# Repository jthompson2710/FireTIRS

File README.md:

# FireTIRS

This respository contains the hardware and software produced during the development of the Fire Thermal InfraRed Spectrometer (FireTIRS) imaging instrument as part of a NASA ESTO FireTech project (grant: 80NSSC23K1544)

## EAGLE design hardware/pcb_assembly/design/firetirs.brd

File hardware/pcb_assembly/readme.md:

## FireTIRS PCB Assembly
This directory contains the design files and documentation necessary to build the FireTIRS PCB Assembly.

* ```design``` : Contains the Eagle version 7.7 CAD source design files (schematic and layout).
* ```documentation``` : Contains supporting documentation files including Bill-of-Material (BOM), component load list, component centroid file, stack-up information and PDF versions of the schematic and layout.
* ```gerbers``` : Contain the PCB gerber files.
* ```stencils``` : Contain the stencil gerber files.

### Printed Circuit Board

* Layer Count: 4
* Material: FR4
* Dimensions: 6.5" x 5.5" (165.1mm x  139.7mm)
* Thickness: 0.062" (1.6mm) thickness

#### Gerber files

| File Suffix | Description |
| --- | --- |
| GBL | Bottom Copper (Layer 4) |
| GBO | Bottom Silkscreen |
| GBS | Bottom Soldermask |
| GL2 | Inner Layer 2 Copper |
| GL3 | Inner Layer 3 Copper |
| GML | Mill layer (dimensional) |
| GTL | Top Copper (Layer 1) |
| GTS | Top Soldermask |
| GTO | Top Silkscreen |
| TXT | Drill file |

### Assembly
The PCB Assembly has surface-mount parts on top and bottom and through-hole parts on top.

(note: Raspberry Pi 4 Compute Module spacers shown are not part of the assembly at this stage)

#### Stencil files
 
| File Suffix | Description |
| --- | --- |
| GBP | Bottom Paste |
| GTP | Top Paste |

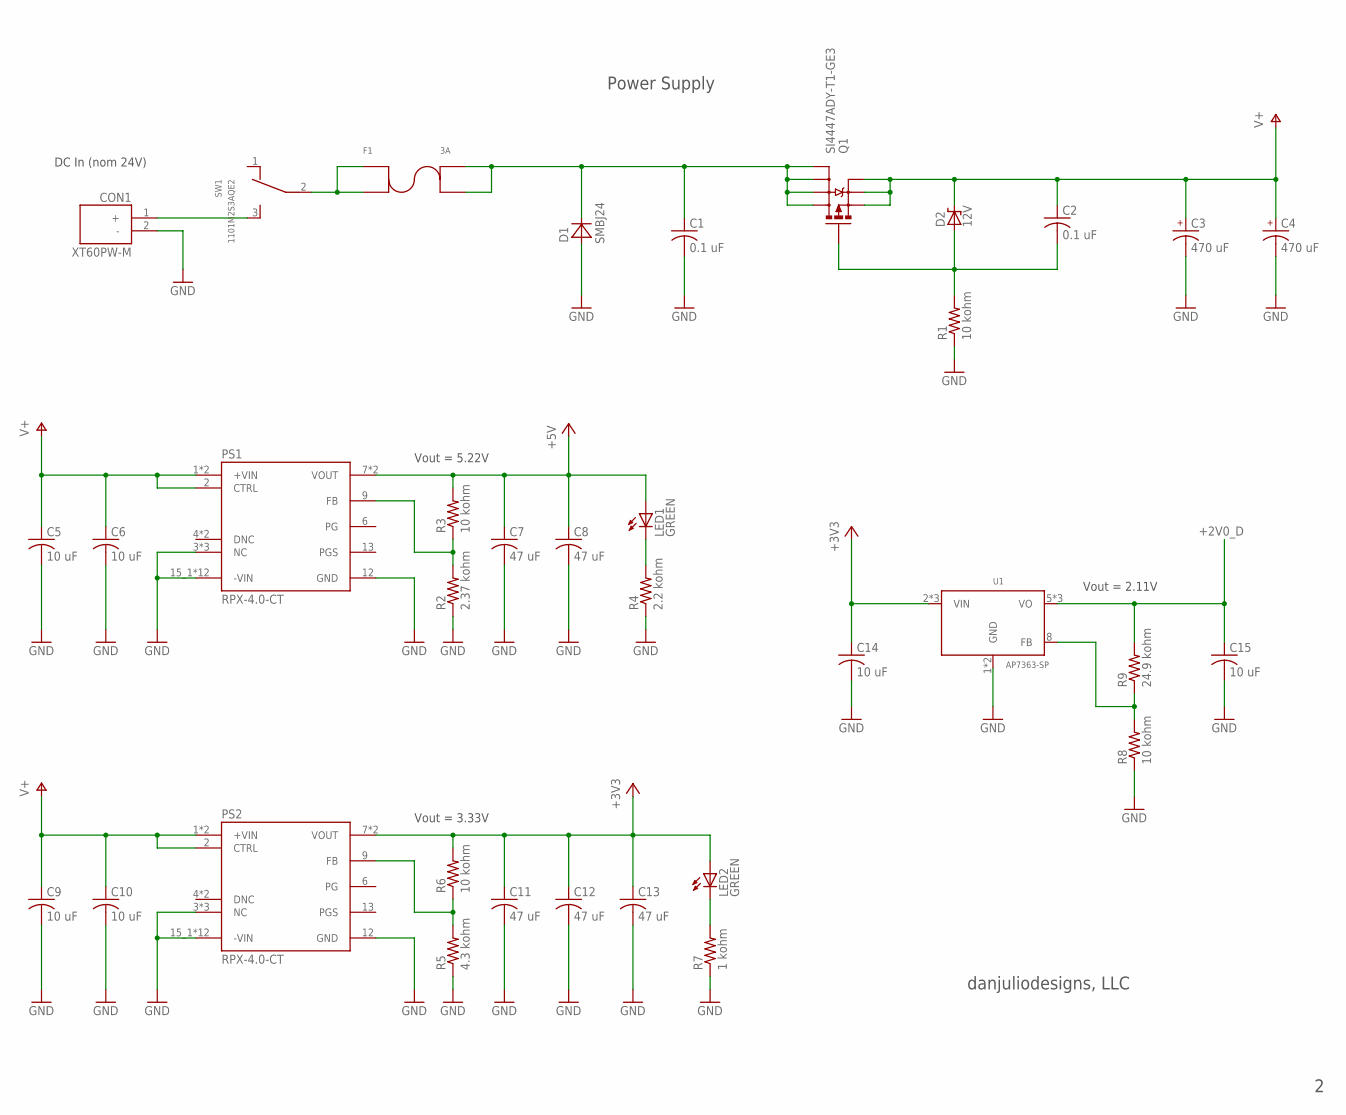
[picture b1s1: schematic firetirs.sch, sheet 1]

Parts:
C1, C2: 0.1 uF; C0805
C3, C4: 470 uF; ECAP-0810
C5, C6, C9, C10: 10 uF; C0805
C7, C8, C11, C12, C13: 47 uF; C0805
C14, C15: 10 uF; C0603
CON1: XT60PW-M; AMASS_XT60PW-M
D1: SMBJ24; DO214AA
D2: 12V; SOD123
F1: 3A; FUSE_5_20_MM_SIDE
LED1, LED2: GREEN; CHIPLED_0603
PS1, PS2: RPX-4.0-CT; CONV_RPX-4.0-CT
Q1: SI4447ADY-T1-GE3; SO8
R1, R3, R6, R8: 10 kohm; R0603
R2: 2.37 kohm; R0603
R4: 2.2 kohm; R0603
R5: 4.3 kohm; R0603
R7: 1 kohm; R0603
R9: 24.9 kohm; R0603
SW1: 1101M2S3AQE2; SIDE_PWR_SPDT
U1: AP7363-SP; SO8_PAD

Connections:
+2V0_D: C15.1, R9.2, U1.5 (VO), U1.6 (VO), U1.7 (VO); also elsewhere on the board
+3V3: C11.1, C12.1, C13.1, C14.1, LED2.A, PS2.7 (VOUT), PS2.8 (VOUT), R6.2, U1.2 (VIN), U1.3 (VIN), U1.4 (VIN); also elsewhere on the board
+5V: C7.1, C8.1, LED1.A, PS1.7 (VOUT), PS1.8 (VOUT), R3.2; also elsewhere on the board
GND: C1.2, C3.- (2), C4.- (2), C5.2, C6.2, C7.2, C8.2, C9.2, C10.2, C11.2, C12.2, C13.2, C14.2, C15.2, CON1.2 (-), D1.A, PS1.3 (NC), PS1.10 (NC), PS1.11 (NC), PS1.12 (GND), PS1.15_1 (-VIN), PS1.15_2 (-VIN), PS1.15_3 (-VIN), PS1.15_4 (-VIN), PS1.15_5 (-VIN), PS1.15_6 (-VIN), PS1.15_7 (-VIN), PS1.15_8 (-VIN), PS1.15_9 (-VIN), PS1.15_10 (-VIN), PS1.15_11 (-VIN), PS1.15_12 (-VIN), PS2.3 (NC), PS2.10 (NC), PS2.11 (NC), PS2.12 (GND), PS2.15_1 (-VIN), PS2.15_2 (-VIN), PS2.15_3 (-VIN), PS2.15_4 (-VIN), PS2.15_5 (-VIN), PS2.15_6 (-VIN), PS2.15_7 (-VIN), PS2.15_8 (-VIN), PS2.15_9 (-VIN), PS2.15_10 (-VIN), PS2.15_11 (-VIN), PS2.15_12 (-VIN), R1.1, R2.1, R4.1, R5.1, R7.1, R8.1, U1.1 (GND), U1.PAD (GND); also elsewhere on the board
unnamed: CON1.1 (+), SW1.3
unnamed: F1.1A (1), F1.1B (2), SW1.2
unnamed: C1.1, D1.C, F1.2A (3), F1.2B (4), Q1.5 (D1), Q1.6 (D2), Q1.7 (D3), Q1.8 (D4)
unnamed: C2.2, D2.A, Q1.4 (G), R1.2
unnamed: LED1.C, R4.2
unnamed: LED2.C, R7.2
unnamed: PS1.9 (FB), R2.2, R3.1
unnamed: R8.2, R9.1, U1.8 (FB)
unnamed: PS2.9 (FB), R5.2, R6.1
V+: C2.1, C3.+ (1), C4.+ (1), C5.1, C6.1, C9.1, C10.1, D2.C, PS1.1 (+VIN), PS1.2 (CTRL), PS1.14 (+VIN), PS2.1 (+VIN), PS2.2 (CTRL), PS2.14 (+VIN), Q1.1 (S1), Q1.2 (S2), Q1.3 (S3)

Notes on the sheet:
Vout = 5.22V
Vout = 3.33V
Power Supply
Vout = 2.11V
DC In (nom 24V)
danjuliodesigns, LLC

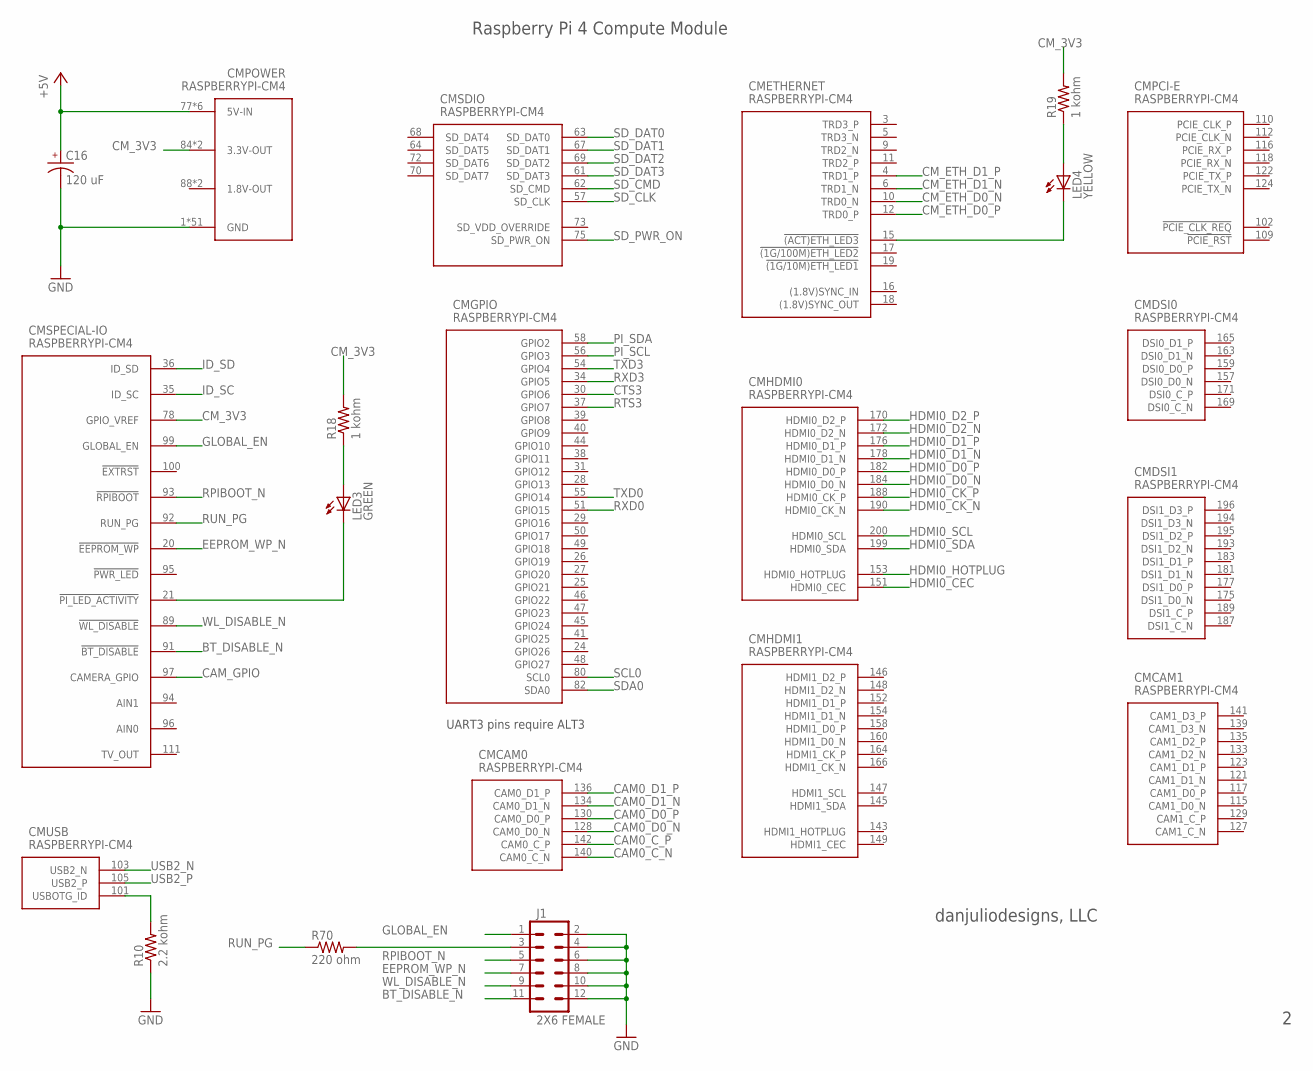
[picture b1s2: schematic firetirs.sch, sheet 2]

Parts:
C16: 120 uF; ECAP-0606
CM: RASPBERRYPI-CM4
J1: 2X6 FEMALE; 2X6
LED3: GREEN; CHIPLED_0603
LED4: YELLOW; CHIPLED_0603
R10: 2.2 kohm; R0603
R18, R19: 1 kohm; R0603
R70: 220 ohm; R0603

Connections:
1.8V-OUT: CM.88 (1.8V-OUT), CM.90 (1.8V-OUT)
+5V: C16.+ (1), CM.77 (5V-IN), CM.79 (5V-IN), CM.81 (5V-IN), CM.83 (5V-IN), CM.85 (5V-IN), CM.87 (5V-IN); also elsewhere on the board
BT_DISABLE_N: CM.91 (!BT_DISABLE), J1.11
CAM0_C_N: CM.140 (CAM0_C_N); also elsewhere on the board
CAM0_C_P: CM.142 (CAM0_C_P); also elsewhere on the board
CAM0_D0_N: CM.128 (CAM0_D0_N); also elsewhere on the board
CAM0_D0_P: CM.130 (CAM0_D0_P); also elsewhere on the board
CAM0_D1_N: CM.134 (CAM0_D1_N); also elsewhere on the board
CAM0_D1_P: CM.136 (CAM0_D1_P); also elsewhere on the board
CAM_GPIO: CM.97 (CAMERA_GPIO); also elsewhere on the board
CM_3V3: CM.78 (GPIO_VREF), CM.84 (3.3V-OUT), CM.86 (3.3V-OUT), R18.2, R19.2; also elsewhere on the board
CM_ETH_D0_N: CM.10 (TRD0_N); also elsewhere on the board
CM_ETH_D0_P: CM.12 (TRD0_P); also elsewhere on the board
CM_ETH_D1_N: CM.6 (TRD1_N); also elsewhere on the board
CM_ETH_D1_P: CM.4 (TRD1_P); also elsewhere on the board
CTS3: CM.30 (GPIO6); also elsewhere on the board
EEPROM_WP_N: CM.20 (!EEPROM_WP), J1.7
GLOBAL_EN: CM.99 (GLOBAL_EN), J1.1
GND: C16.- (2), CM.1 (GND), CM.2 (GND), CM.7 (GND), CM.8 (GND), CM.13 (GND), CM.14 (GND), CM.22 (GND), CM.23 (GND), CM.32 (GND), CM.33 (GND), CM.42 (GND), CM.43 (GND), CM.52 (GND), CM.53 (GND), CM.59 (GND), CM.60 (GND), CM.65 (GND), CM.66 (GND), CM.71 (GND), CM.74 (GND), CM.98 (GND), CM.107 (GND), CM.108 (GND), CM.113 (GND), CM.114 (GND), CM.119 (GND), CM.120 (GND), CM.125 (GND), CM.126 (GND), CM.131 (GND), CM.132 (GND), CM.137 (GND), CM.138 (GND), CM.144 (GND), CM.150 (GND), CM.155 (GND), CM.156 (GND), CM.161 (GND), CM.162 (GND), CM.167 (GND), CM.168 (GND), CM.173 (GND), CM.174 (GND), CM.179 (GND), CM.180 (GND), CM.185 (GND), CM.186 (GND), CM.191 (GND), CM.192 (GND), CM.197 (GND), CM.198 (GND), J1.2, J1.4, J1.6, J1.8, J1.10, J1.12, R10.1; also elsewhere on the board
HDMI0_CEC: CM.151 (HDMI0_CEC); also elsewhere on the board
HDMI0_CK_N: CM.190 (HDMI0_CK_N); also elsewhere on the board
HDMI0_CK_P: CM.188 (HDMI0_CK_P); also elsewhere on the board
HDMI0_D0_N: CM.184 (HDMI0_D0_N); also elsewhere on the board
HDMI0_D0_P: CM.182 (HDMI0_D0_P); also elsewhere on the board
HDMI0_D1_N: CM.178 (HDMI0_D1_N); also elsewhere on the board
HDMI0_D1_P: CM.176 (HDMI0_D1_P); also elsewhere on the board
HDMI0_D2_N: CM.172 (HDMI0_D2_N); also elsewhere on the board
HDMI0_D2_P: CM.170 (HDMI0_D2_P); also elsewhere on the board
HDMI0_HOTPLUG: CM.153 (HDMI0_HOTPLUG); also elsewhere on the board
HDMI0_SCL: CM.200 (HDMI0_SCL); also elsewhere on the board
HDMI0_SDA: CM.199 (HDMI0_SDA); also elsewhere on the board
ID_SC: CM.35 (ID_SC); also elsewhere on the board
ID_SD: CM.36 (ID_SD); also elsewhere on the board
unnamed: CM.101 (USBOTG_ID), R10.2
unnamed: CM.21 (!PI_LED_ACTIVITY), LED3.C
unnamed: LED3.A, R18.1
unnamed: CM.15 (!(ACT)ETH_LED3), LED4.C
unnamed: LED4.A, R19.1
unnamed: J1.3, R70.2
PI_SCL: CM.56 (GPIO3); also elsewhere on the board
PI_SDA: CM.58 (GPIO2); also elsewhere on the board
RPIBOOT_N: CM.93 (!RPIBOOT), J1.5
RTS3: CM.37 (GPIO7); also elsewhere on the board
RUN_PG: CM.92 (RUN_PG), R70.1
RXD0: CM.51 (GPIO15); also elsewhere on the board
RXD3: CM.34 (GPIO5); also elsewhere on the board
SCL0: CM.80 (SCL0); also elsewhere on the board
SDA0: CM.82 (SDA0); also elsewhere on the board
SD_CLK: CM.57 (SD_CLK); also elsewhere on the board
SD_CMD: CM.62 (SD_CMD); also elsewhere on the board
SD_DAT0: CM.63 (SD_DAT0); also elsewhere on the board
SD_DAT1: CM.67 (SD_DAT1); also elsewhere on the board
SD_DAT2: CM.69 (SD_DAT2); also elsewhere on the board
SD_DAT3: CM.61 (SD_DAT3); also elsewhere on the board
SD_PWR_ON: CM.75 (SD_PWR_ON); also elsewhere on the board
TXD0: CM.55 (GPIO14); also elsewhere on the board
TXD3: CM.54 (GPIO4); also elsewhere on the board
USB2_N: CM.103 (USB2_N); also elsewhere on the board
USB2_P: CM.105 (USB2_P); also elsewhere on the board
WL_DISABLE_N: CM.89 (!WL_DISABLE), J1.9

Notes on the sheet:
Raspberry Pi 4 Compute Module
UART3 pins require ALT3
danjuliodesigns, LLC

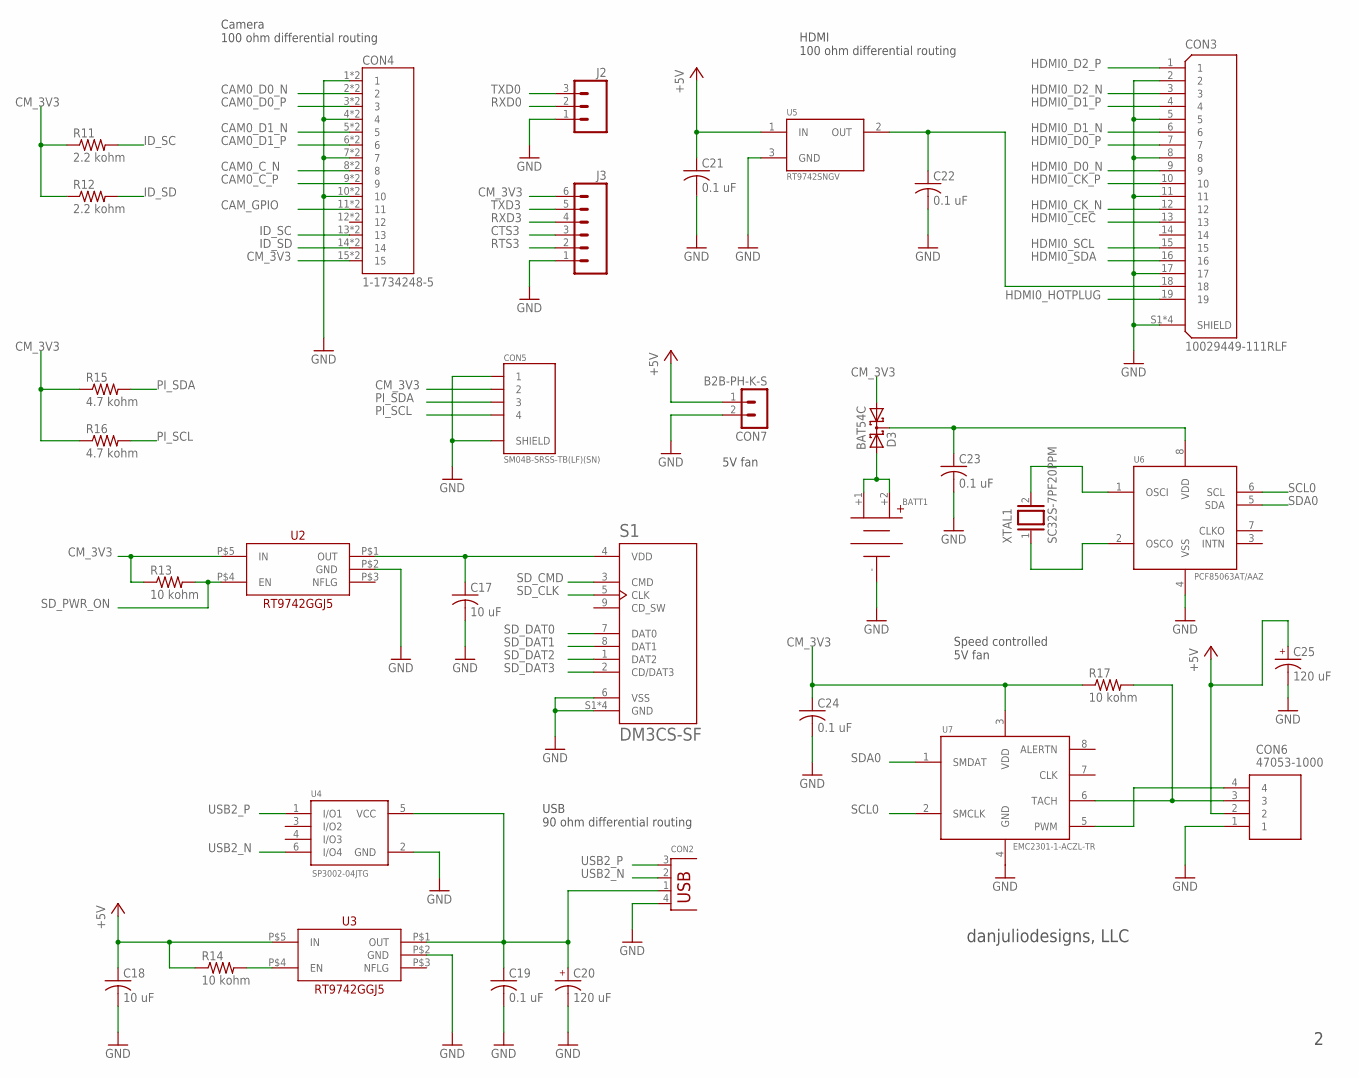
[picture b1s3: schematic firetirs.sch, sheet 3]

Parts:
BATT1: COIN_CELL12MM; KEYSTONE_3001
C17, C18: 10 uF; C0603
C19, C21, C22, C23, C24: 0.1 uF; C0603
C20, C25: 120 uF; ECAP-0606
CON2: USBFCI_87520; FCI_87520
CON3: 10029449-111RLF; AMPHENOL_10029449-111RLF
CON4: 1-1734248-5; TE_1-1734248-5
CON5: SM04B-SRSS-TB(LF)(SN); JST_SM04B-SRSS-TB(LF)(SN)
CON6: 47053-1000; 470531000
CON7: B2B-PH-K-S
D3: BAT54C; SOT23
J2: M03PTH; 1X03
J3: M06SILK_FEMALE_PTH; 1X06
R11, R12: 2.2 kohm; R0603
R13, R14, R17: 10 kohm; R0603
R15, R16: 4.7 kohm; R0603
S1: DM3CS-SF; HRS_DM3CS-SF
U2, U3: RT9742GGJ5; TSOT-23-5
U4: SP3002-04JTG; SOT65P220X95-6N
U5: RT9742SNGV; SOT23-3
U6: PCF85063AT/AAZ; SO8
U7: EMC2301-1-ACZL-TR; MSOP8
XTAL1: SC32S-7PF20PPM; CRYSTAL-3215

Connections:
+5V: C18.1, C21.1, C25.+ (1), CON6.2, CON7.1, R14.1, U3.P$5 (IN), U5.1 (IN); also elsewhere on the board
CAM0_C_N: CON4.8, CON4.8_1 (8); also elsewhere on the board
CAM0_C_P: CON4.9, CON4.9_1 (9); also elsewhere on the board
CAM0_D0_N: CON4.2, CON4.2_1 (2); also elsewhere on the board
CAM0_D0_P: CON4.3, CON4.3_1 (3); also elsewhere on the board
CAM0_D1_N: CON4.5, CON4.5_1 (5); also elsewhere on the board
CAM0_D1_P: CON4.6, CON4.6_1 (6); also elsewhere on the board
CAM_GPIO: CON4.11, CON4.11_1 (11); also elsewhere on the board
CM_3V3: C24.1, CON4.15, CON4.15_1 (15), CON5.2, D3.1 (A1), J3.6, R11.1, R12.1, R13.1, R15.1, R16.1, R17.1, U2.P$5 (IN), U7.3 (VDD); also elsewhere on the board
CTS3: J3.3; also elsewhere on the board
GND: BATT1.-, C17.2, C18.2, C19.2, C20.- (2), C21.2, C22.2, C23.2, C24.2, C25.- (2), CON2.4 (GND), CON3.2, CON3.5, CON3.8, CON3.11, CON3.17, CON3.S1 (SHIELD), CON3.S2 (SHIELD), CON3.S3 (SHIELD), CON3.S4 (SHIELD), CON4.1, CON4.1_1 (1), CON4.4, CON4.4_1 (4), CON4.7, CON4.7_1 (7), CON4.10, CON4.10_1 (10), CON5.1, CON5.S1 (SHIELD), CON5.S2 (SHIELD), CON6.1, CON7.2, J2.1, J3.1, S1.6 (VSS), S1.S1 (GND), S1.S2 (GND), S1.S3 (GND), S1.S5 (GND), U2.P$2 (GND), U3.P$2 (GND), U4.2 (GND), U5.3 (GND), U6.4 (VSS), U7.4 (GND); also elsewhere on the board
HDMI0_CEC: CON3.13; also elsewhere on the board
HDMI0_CK_N: CON3.12; also elsewhere on the board
HDMI0_CK_P: CON3.10; also elsewhere on the board
HDMI0_D0_N: CON3.9; also elsewhere on the board
HDMI0_D0_P: CON3.7; also elsewhere on the board
HDMI0_D1_N: CON3.6; also elsewhere on the board
HDMI0_D1_P: CON3.4; also elsewhere on the board
HDMI0_D2_N: CON3.3; also elsewhere on the board
HDMI0_D2_P: CON3.1; also elsewhere on the board
HDMI0_HOTPLUG: CON3.19; also elsewhere on the board
HDMI0_SCL: CON3.15; also elsewhere on the board
HDMI0_SDA: CON3.16; also elsewhere on the board
ID_SC: CON4.13, CON4.13_1 (13), R11.2; also elsewhere on the board
ID_SD: CON4.14, CON4.14_1 (14), R12.2; also elsewhere on the board
unnamed: C17.1, S1.4 (VDD), U2.P$1 (OUT)
unnamed: C19.1, C20.+ (1), CON2.1 (VBUS), U3.P$1 (OUT), U4.5 (VCC)
unnamed: U6.2 (OSCO), XTAL1.1
unnamed: BATT1.+1, BATT1.+2, D3.2 (A2)
unnamed: U6.1 (OSCI), XTAL1.2
unnamed: CON6.3, R17.2, U7.6 (TACH)
unnamed: CON6.4, U7.5 (PWM)
unnamed: R14.2, U3.P$4 (EN)
OUT: C22.1, CON3.18, U5.2 (OUT)
PI_SCL: CON5.4, R16.2; also elsewhere on the board
PI_SDA: CON5.3, R15.2; also elsewhere on the board
RTS3: J3.2; also elsewhere on the board
RXD0: J2.2; also elsewhere on the board
RXD3: J3.4; also elsewhere on the board
SCL0: U6.6 (SCL), U7.2 (SMCLK); also elsewhere on the board
SDA0: U6.5 (SDA), U7.1 (SMDAT); also elsewhere on the board
SD_CLK: S1.5 (CLK); also elsewhere on the board
SD_CMD: S1.3 (CMD); also elsewhere on the board
SD_DAT0: S1.7 (DAT0); also elsewhere on the board
SD_DAT1: S1.8 (DAT1); also elsewhere on the board
SD_DAT2: S1.1 (DAT2); also elsewhere on the board
SD_DAT3: S1.2 (CD/DAT3); also elsewhere on the board
SD_PWR_ON: R13.2, U2.P$4 (EN); also elsewhere on the board
TXD0: J2.3; also elsewhere on the board
TXD3: J3.5; also elsewhere on the board
USB2_N: CON2.2 (D-), U4.6 (I/O4); also elsewhere on the board
USB2_P: CON2.3 (D+), U4.1 (I/O1); also elsewhere on the board
VDD: C23.1, D3.3 (CC), U6.8 (VDD)

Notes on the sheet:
Camera 100 ohm differential routing
USB 90 ohm differential routing
HDMI 100 ohm differential routing
Speed controlled 5V fan
5V fan
danjuliodesigns, LLC

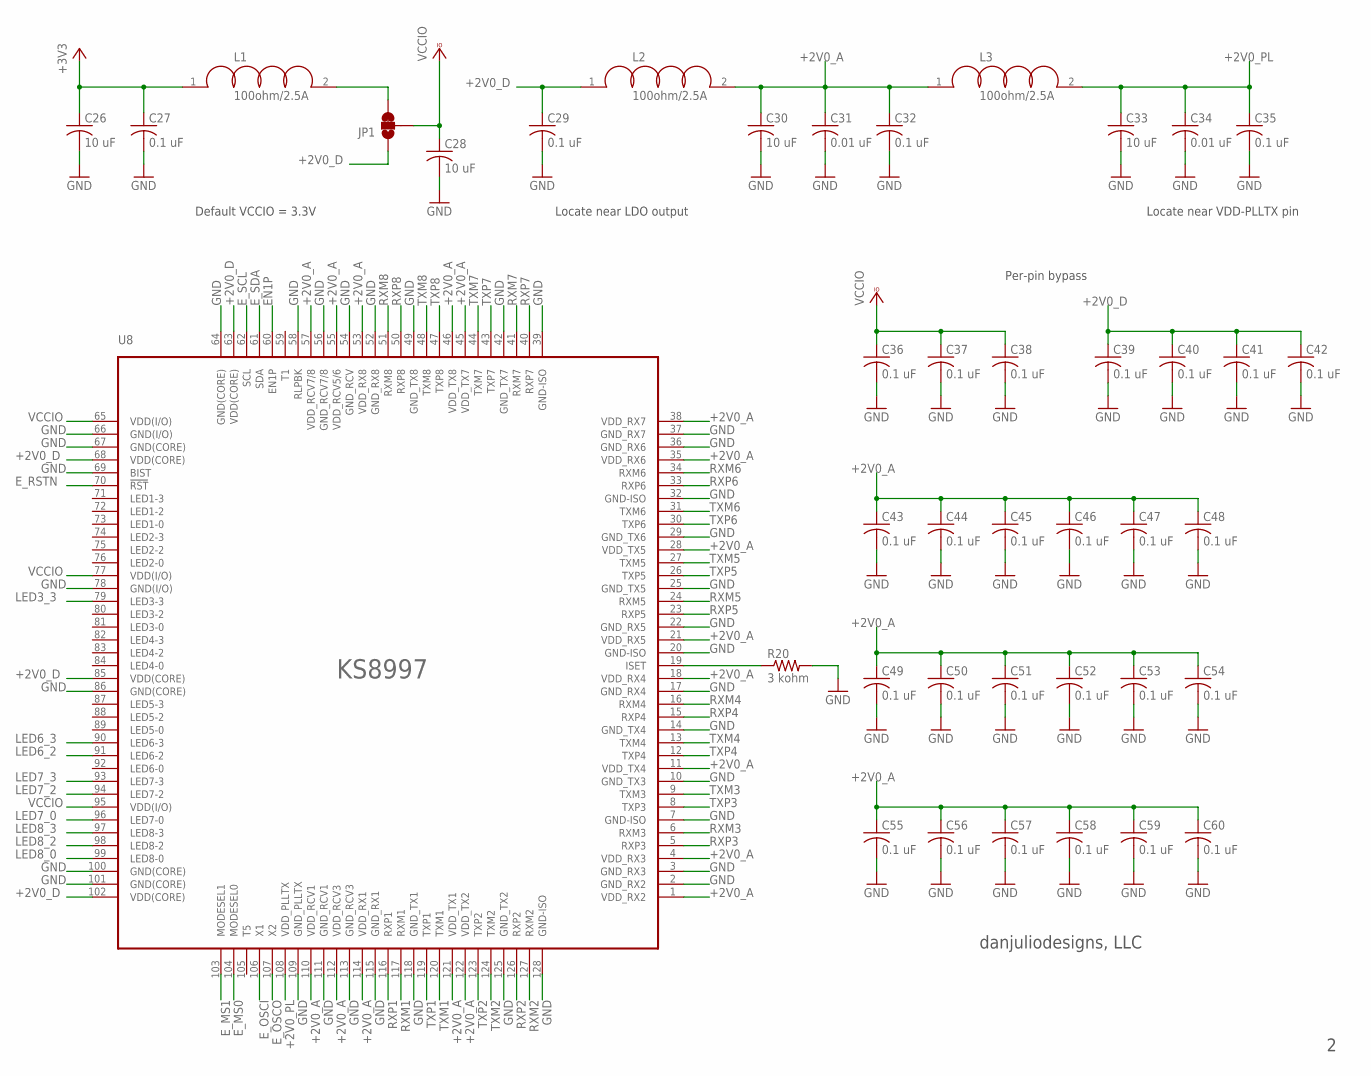
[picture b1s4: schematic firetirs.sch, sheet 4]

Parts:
C26, C28, C30, C33: 10 uF; C0603
C27, C29, C32, C35, C36, C37, C38, C39, C40, C41, C42, C43, C44, C45, C46, C47, C48, C49, C50, C51, C52, C53, C54, C55, C56, C57, C58, C59, C60: 0.1 uF; C0603
C31, C34: 0.01 uF; C0603
JP1: JUMPER-PAD-3-2OF3_NC_BY_TRACE_SMALL; PAD-JUMPER-3-2OF3_NC_BY_TRACE_YES_SILK_FULL_BOX
L1, L2, L3: 100ohm/2.5A; L0603
R20: 3 kohm; R0603
U8: KS8997; PQFP128-PQ

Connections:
+2V0_A: C30.1, C31.1, C32.1, C43.1, C44.1, C45.1, C46.1, C47.1, C48.1, C49.1, C50.1, C51.1, C52.1, C53.1, C54.1, C55.1, C56.1, C57.1, C58.1, C59.1, C60.1, L2.2, L3.1, U8.1 (VDD_RX2), U8.4 (VDD_RX3), U8.11 (VDD_TX4), U8.18 (VDD_RX4), U8.21 (VDD_RX5), U8.28 (VDD_TX5), U8.35 (VDD_RX6), U8.38 (VDD_RX7), U8.45 (VDD_TX7), U8.46 (VDD_TX8), U8.53 (VDD_RX8), U8.55 (VDD_RCV5/6), U8.57 (VDD_RCV7/8), U8.110 (VDD_RCV1), U8.112 (VDD_RCV3), U8.114 (VDD_RX1), U8.121 (VDD_TX1), U8.122 (VDD_TX2); also elsewhere on the board
+2V0_D: C29.1, C39.1, C40.1, C41.1, C42.1, JP1.1, L2.1, U8.63 (VDD(CORE)), U8.68 (VDD(CORE)), U8.85 (VDD(CORE)), U8.102 (VDD(CORE)); also elsewhere on the board
+2V0_PL: C33.1, C34.1, C35.1, L3.2, U8.108 (VDD_PLLTX)
+3V3: C26.1, C27.1, L1.1; also elsewhere on the board
EN1P: U8.60 (EN1P); also elsewhere on the board
E_MS0: U8.104 (MODESEL0); also elsewhere on the board
E_MS1: U8.103 (MODESEL1); also elsewhere on the board
E_OSCI: U8.106 (X1); also elsewhere on the board
E_OSCO: U8.107 (X2); also elsewhere on the board
E_RSTN: U8.70 (!RST!); also elsewhere on the board
E_SCL: U8.62 (SCL); also elsewhere on the board
E_SDA: U8.61 (SDA); also elsewhere on the board
GND: C26.2, C27.2, C28.2, C29.2, C30.2, C31.2, C32.2, C33.2, C34.2, C35.2, C36.2, C37.2, C38.2, C39.2, C40.2, C41.2, C42.2, C43.2, C44.2, C45.2, C46.2, C47.2, C48.2, C49.2, C50.2, C51.2, C52.2, C53.2, C54.2, C55.2, C56.2, C57.2, C58.2, C59.2, C60.2, R20.2, U8.2 (GND_RX2), U8.3 (GND_RX3), U8.7 (GND-ISO), U8.10 (GND_TX3), U8.14 (GND_TX4), U8.17 (GND_RX4), U8.20 (GND-ISO), U8.22 (GND_RX5), U8.25 (GND_TX5), U8.29 (GND_TX6), U8.32 (GND-ISO), U8.36 (GND_RX6), U8.37 (GND_RX7), U8.39 (GND-ISO), U8.42 (GND_TX7), U8.49 (GND_TX8), U8.52 (GND_RX8), U8.54 (GND_RCV), U8.56 (GND_RCV7/8), U8.58 (RLPBK), U8.64 (GND(CORE)), U8.66 (GND(I/O)), U8.67 (GND(CORE)), U8.69 (BIST), U8.78 (GND(I/O)), U8.86 (GND(CORE)), U8.100 (GND(CORE)), U8.101 (GND(CORE)), U8.109 (GND_PLLTX), U8.111 (GND_RCV1), U8.113 (GND_RCV3), U8.115 (GND_RX1), U8.118 (GND_TX1), U8.125 (GND_TX2), U8.128 (GND-ISO); also elsewhere on the board
ISET: R20.1, U8.19 (ISET)
LED3_3: U8.79 (LED3-3); also elsewhere on the board
LED6_2: U8.91 (LED6-2); also elsewhere on the board
LED6_3: U8.90 (LED6-3); also elsewhere on the board
LED7_0: U8.96 (LED7-0); also elsewhere on the board
LED7_2: U8.94 (LED7-2); also elsewhere on the board
LED7_3: U8.93 (LED7-3); also elsewhere on the board
LED8_0: U8.99 (LED8-0); also elsewhere on the board
LED8_2: U8.98 (LED8-2); also elsewhere on the board
LED8_3: U8.97 (LED8-3); also elsewhere on the board
unnamed: JP1.3, L1.2
RXM1: U8.117 (RXM1); also elsewhere on the board
RXM2: U8.127 (RXM2); also elsewhere on the board
RXM3: U8.6 (RXM3); also elsewhere on the board
RXM4: U8.16 (RXM4); also elsewhere on the board
RXM5: U8.24 (RXM5); also elsewhere on the board
RXM6: U8.34 (RXM6); also elsewhere on the board
RXM7: U8.41 (RXM7); also elsewhere on the board
RXM8: U8.51 (RXM8); also elsewhere on the board
RXP1: U8.116 (RXP1); also elsewhere on the board
RXP2: U8.126 (RXP2); also elsewhere on the board
RXP3: U8.5 (RXP3); also elsewhere on the board
RXP4: U8.15 (RXP4); also elsewhere on the board
RXP5: U8.23 (RXP5); also elsewhere on the board
RXP6: U8.33 (RXP6); also elsewhere on the board
RXP7: U8.40 (RXP7); also elsewhere on the board
RXP8: U8.50 (RXP8); also elsewhere on the board
TXM1: U8.120 (TXM1); also elsewhere on the board
TXM2: U8.124 (TXM2); also elsewhere on the board
TXM3: U8.9 (TXM3); also elsewhere on the board
TXM4: U8.13 (TXM4); also elsewhere on the board
TXM5: U8.27 (TXM5); also elsewhere on the board
TXM6: U8.31 (TXM6); also elsewhere on the board
TXM7: U8.44 (TXM7); also elsewhere on the board
TXM8: U8.48 (TXM8); also elsewhere on the board
TXP1: U8.119 (TXP1); also elsewhere on the board
TXP2: U8.123 (TXP2); also elsewhere on the board
TXP3: U8.8 (TXP3); also elsewhere on the board
TXP4: U8.12 (TXP4); also elsewhere on the board
TXP5: U8.26 (TXP5); also elsewhere on the board
TXP6: U8.30 (TXP6); also elsewhere on the board
TXP7: U8.43 (TXP7); also elsewhere on the board
TXP8: U8.47 (TXP8); also elsewhere on the board
VCCIO: C28.1, C36.1, C37.1, C38.1, JP1.2, U8.65 (VDD(I/O)), U8.77 (VDD(I/O)), U8.95 (VDD(I/O)); also elsewhere on the board

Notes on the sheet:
Locate near LDO output
Locate near VDD-PLLTX pin
Per-pin bypass
danjuliodesigns, LLC
Default VCCIO = 3.3V

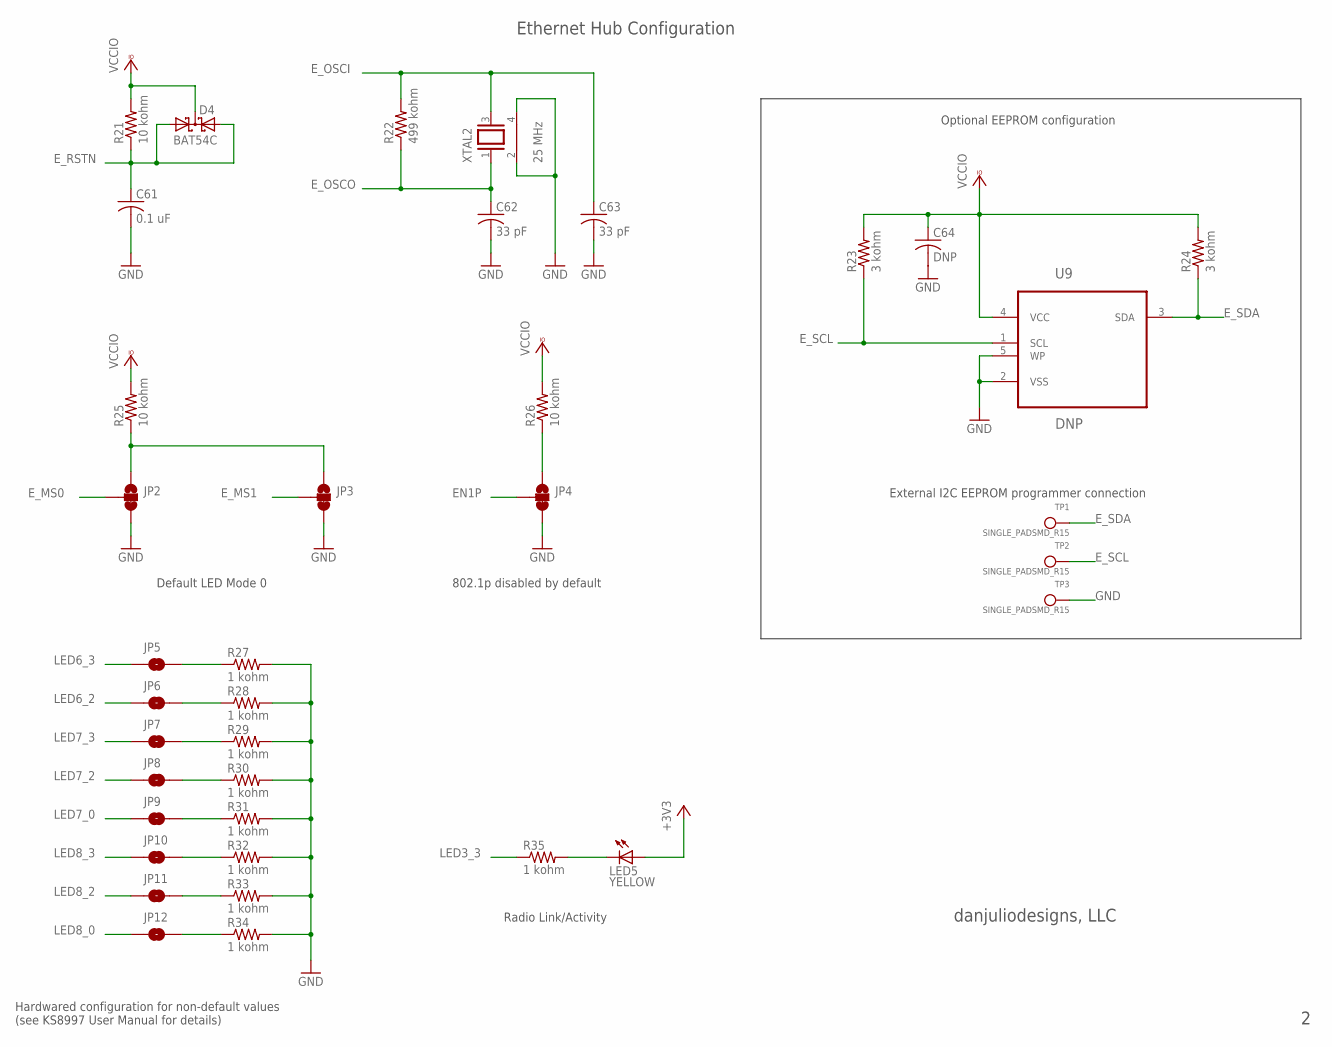
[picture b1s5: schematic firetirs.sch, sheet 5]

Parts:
C61: 0.1 uF; C0603
C62, C63: 33 pF; C0603
C64: DNP; C0603
D4: BAT54C; SOT23
JP2, JP3, JP4: JUMPER-PAD-3-2OF3_NC_BY_TRACE_SMALL; PAD-JUMPER-3-2OF3_NC_BY_TRACE_YES_SILK_FULL_BOX
JP5, JP6, JP7, JP8, JP9, JP10, JP11, JP12: JUMPER-PAD-2-NOYES_SILK; PAD-JUMPER-2-NO_YES_SILK
LED5: YELLOW; CHIPLED_0603
R21, R25, R26: 10 kohm; R0603
R22: 499 kohm; R0603
R23, R24: 3 kohm; R0603
R27, R28, R29, R30, R31, R32, R33, R34, R35: 1 kohm; R0603
TP1, TP2, TP3: SINGLE_PADSMD_R15; 1_5MM_R_SMD_PAD
U9: DNP; SOT95P270X145-5N
XTAL2: 25 MHz; CRYSTAL-3225

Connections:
+3V3: LED5.A; also elsewhere on the board
EN1P: JP4.2; also elsewhere on the board
E_MS0: JP2.2; also elsewhere on the board
E_MS1: JP3.2; also elsewhere on the board
E_OSCI: C63.1, R22.2, XTAL2.3; also elsewhere on the board
E_OSCO: C62.1, R22.1, XTAL2.1; also elsewhere on the board
E_RSTN: C61.1, D4.1 (A1), D4.2 (A2), R21.1; also elsewhere on the board
E_SCL: R23.1, TP2.P$1, U9.1 (SCL); also elsewhere on the board
E_SDA: R24.1, TP1.P$1, U9.3 (SDA); also elsewhere on the board
GND: C61.2, C62.2, C63.2, C64.2, JP2.3, JP3.3, JP4.3, R27.2, R28.2, R29.2, R30.2, R31.2, R32.2, R33.2, R34.2, TP3.P$1, U9.2 (VSS), U9.5 (WP), XTAL2.2, XTAL2.4; also elsewhere on the board
LED3_3: R35.1; also elsewhere on the board
LED6_2: JP6.1; also elsewhere on the board
LED6_3: JP5.1; also elsewhere on the board
LED7_0: JP9.1; also elsewhere on the board
LED7_2: JP8.1; also elsewhere on the board
LED7_3: JP7.1; also elsewhere on the board
LED8_0: JP12.1; also elsewhere on the board
LED8_2: JP11.1; also elsewhere on the board
LED8_3: JP10.1; also elsewhere on the board
unnamed: JP2.1, JP3.1, R25.1
unnamed: JP4.1, R26.1
unnamed: JP5.2, R27.1
unnamed: JP6.2, R28.1
unnamed: JP7.2, R29.1
unnamed: JP8.2, R30.1
unnamed: JP9.2, R31.1
unnamed: JP10.2, R32.1
unnamed: JP11.2, R33.1
unnamed: JP12.2, R34.1
unnamed: LED5.C, R35.2
VCCIO: C64.1, D4.3 (CC), R21.2, R23.2, R24.2, R25.2, R26.2, U9.4 (VCC); also elsewhere on the board

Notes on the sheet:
Radio Link/Activity
Optional EEPROM configuration
Default LED Mode 0
802.1p disabled by default
Hardwared configuration for non-default values (see KS8997 User Manual for details)
External I2C EEPROM programmer connection
danjuliodesigns, LLC
Ethernet Hub Configuration

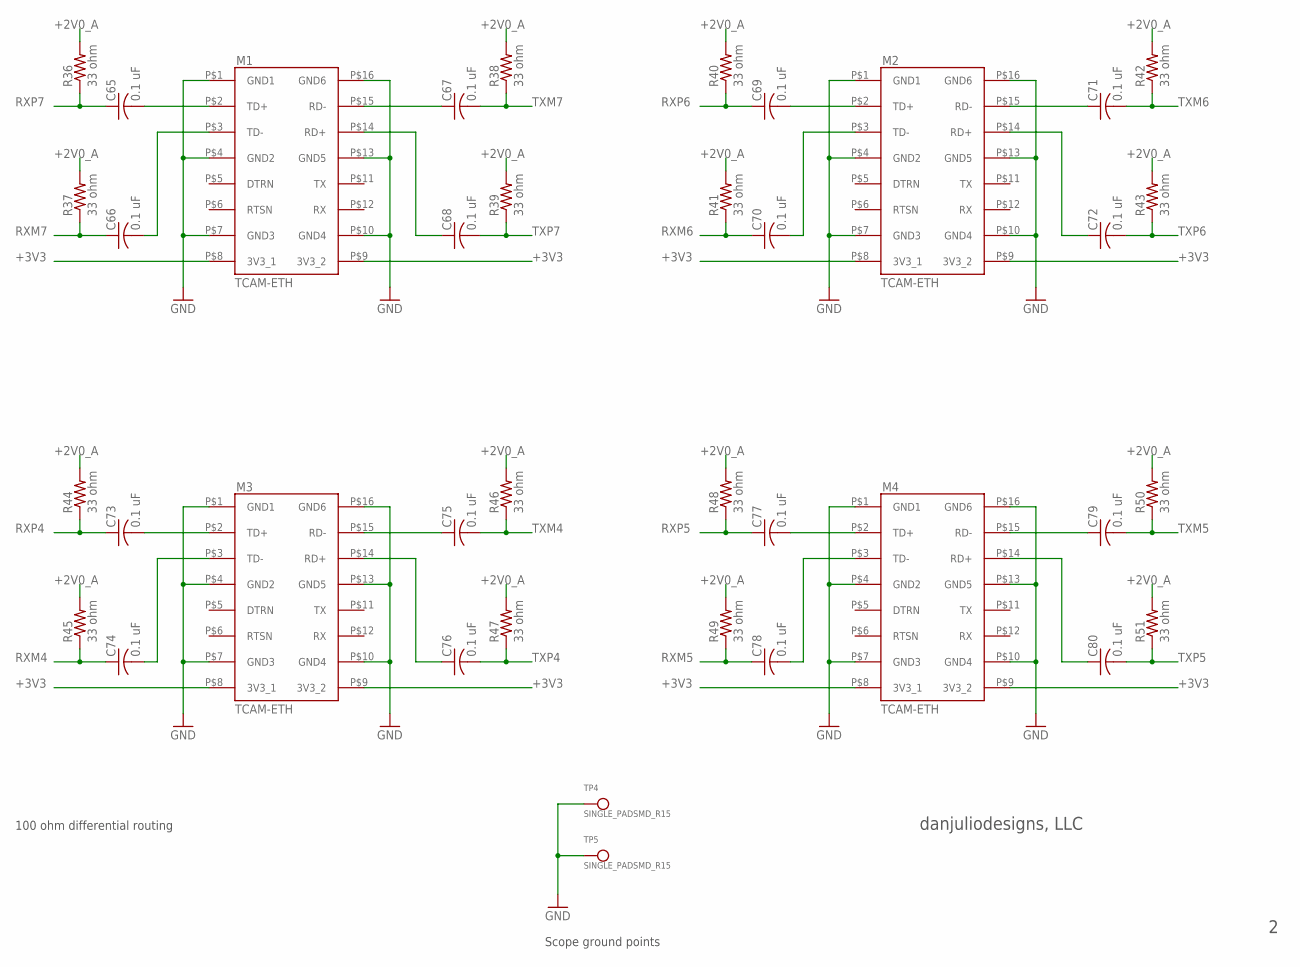
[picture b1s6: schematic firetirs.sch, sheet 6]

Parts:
C65, C66, C67, C68, C69, C70, C71, C72, C73, C74, C75, C76, C77, C78, C79, C80: 0.1 uF; C0603
M1, M2, M3, M4: TCAM-ETH
R36, R37, R38, R39, R40, R41, R42, R43, R44, R45, R46, R47, R48, R49, R50, R51: 33 ohm; R0603
TP4, TP5: SINGLE_PADSMD_R15; 1_5MM_R_SMD_PAD

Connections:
+2V0_A: R36.2, R37.2, R38.2, R39.2, R40.2, R41.2, R42.2, R43.2, R44.2, R45.2, R46.2, R47.2, R48.2, R49.2, R50.2, R51.2; also elsewhere on the board
+3V3: M1.P$8 (3V3_1), M1.P$9 (3V3_2), M2.P$8 (3V3_1), M2.P$9 (3V3_2), M3.P$8 (3V3_1), M3.P$9 (3V3_2), M4.P$8 (3V3_1), M4.P$9 (3V3_2); also elsewhere on the board
GND: M1.P$1 (GND1), M1.P$4 (GND2), M1.P$7 (GND3), M1.P$10 (GND4), M1.P$13 (GND5), M1.P$16 (GND6), M2.P$1 (GND1), M2.P$4 (GND2), M2.P$7 (GND3), M2.P$10 (GND4), M2.P$13 (GND5), M2.P$16 (GND6), M3.P$1 (GND1), M3.P$4 (GND2), M3.P$7 (GND3), M3.P$10 (GND4), M3.P$13 (GND5), M3.P$16 (GND6), M4.P$1 (GND1), M4.P$4 (GND2), M4.P$7 (GND3), M4.P$10 (GND4), M4.P$13 (GND5), M4.P$16 (GND6), TP4.P$1, TP5.P$1; also elsewhere on the board
unnamed: C70.2, M2.P$3 (TD-)
unnamed: C66.2, M1.P$3 (TD-)
unnamed: C65.2, M1.P$2 (TD+)
unnamed: C69.2, M2.P$2 (TD+)
unnamed: C71.1, M2.P$15 (RD-)
unnamed: C67.1, M1.P$15 (RD-)
unnamed: C68.1, M1.P$14 (RD+)
unnamed: C72.1, M2.P$14 (RD+)
unnamed: C74.2, M3.P$3 (TD-)
unnamed: C73.2, M3.P$2 (TD+)
unnamed: C75.1, M3.P$15 (RD-)
unnamed: C76.1, M3.P$14 (RD+)
unnamed: C78.2, M4.P$3 (TD-)
unnamed: C77.2, M4.P$2 (TD+)
unnamed: C79.1, M4.P$15 (RD-)
unnamed: C80.1, M4.P$14 (RD+)
RXM4: C74.1, R45.1; also elsewhere on the board
RXM5: C78.1, R49.1; also elsewhere on the board
RXM6: C70.1, R41.1; also elsewhere on the board
RXM7: C66.1, R37.1; also elsewhere on the board
RXP4: C73.1, R44.1; also elsewhere on the board
RXP5: C77.1, R48.1; also elsewhere on the board
RXP6: C69.1, R40.1; also elsewhere on the board
RXP7: C65.1, R36.1; also elsewhere on the board
TXM4: C75.2, R46.1; also elsewhere on the board
TXM5: C79.2, R50.1; also elsewhere on the board
TXM6: C71.2, R42.1; also elsewhere on the board
TXM7: C67.2, R38.1; also elsewhere on the board
TXP4: C76.2, R47.1; also elsewhere on the board
TXP5: C80.2, R51.1; also elsewhere on the board
TXP6: C72.2, R43.1; also elsewhere on the board
TXP7: C68.2, R39.1; also elsewhere on the board

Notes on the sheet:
100 ohm differential routing
danjuliodesigns, LLC
Scope ground points

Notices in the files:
parts and their libraries:
SparkFun-Connectors: Licensing: Creative Commons ShareAlike 4.0 International - https://creativecommons.org/licenses/by-sa/4.0
